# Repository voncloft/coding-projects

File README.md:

# Coding projects

A single-repository backup of the projects in this directory. Each project is stored here as ordinary files, so a clone or GitHub source download includes the project contents without submodules.

This repository starts with one snapshot of the current files. Earlier individual-project Git histories are not imported.

## Restore

```sh
git clone git@github.com:voncloft/coding-projects.git
cd coding-projects
```

Each project has its own build instructions and dependencies. Source code, required assets, CAD designs, firmware sources, and documentation are included. Build directories, compiled programs and libraries, firmware images, packaged browser extensions, runtime logs, local credentials, and development caches are excluded. Reinstall dependencies, rebuild the projects, and restore any credentials separately after reinstalling the OS.

## Update the backup

Run these commands from the top-level `coding-projects` directory:

```sh
git add -A
git commit -m "Update project backup"
git push
```

The projects retain their individual licenses and third-party notices. The keyboard project's existing engineering-audit and manufacturing-hold status is unchanged.

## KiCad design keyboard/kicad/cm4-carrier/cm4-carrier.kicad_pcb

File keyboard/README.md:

# Keyboard Revision H engineering audit

**Manufacturing HOLD. No approved replacement supplier ZIP.**

Start with [START-HERE.md](START-HERE.md), [current checks](CHECK-RESULTS.md) and [open items](OPEN-ITEMS.md). This folder holds the current KiCad, enclosure, parts, firmware and software work. Revision G must not be built.

Passing rule checks and software fixtures do not establish hardware qualification. Outstanding electrical review items and all physical acceptance measurements remain open. The owner’s live system has not been installed to, flashed or reconfigured.

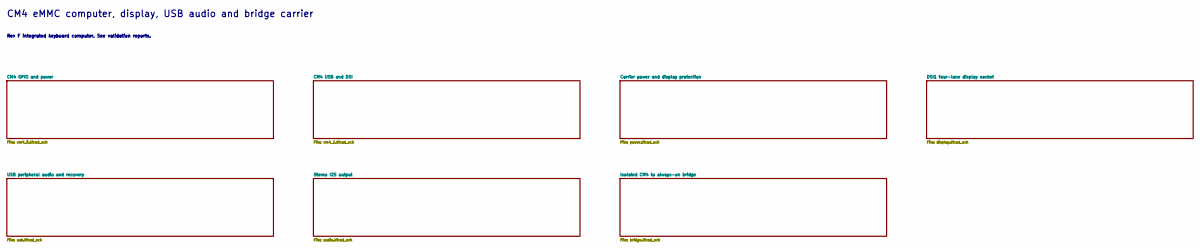
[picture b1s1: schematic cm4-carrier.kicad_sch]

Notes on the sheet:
CM4 eMMC computer, display, USB audio and bridge carrier
Rev F integrated keyboard computer. See validation reports.

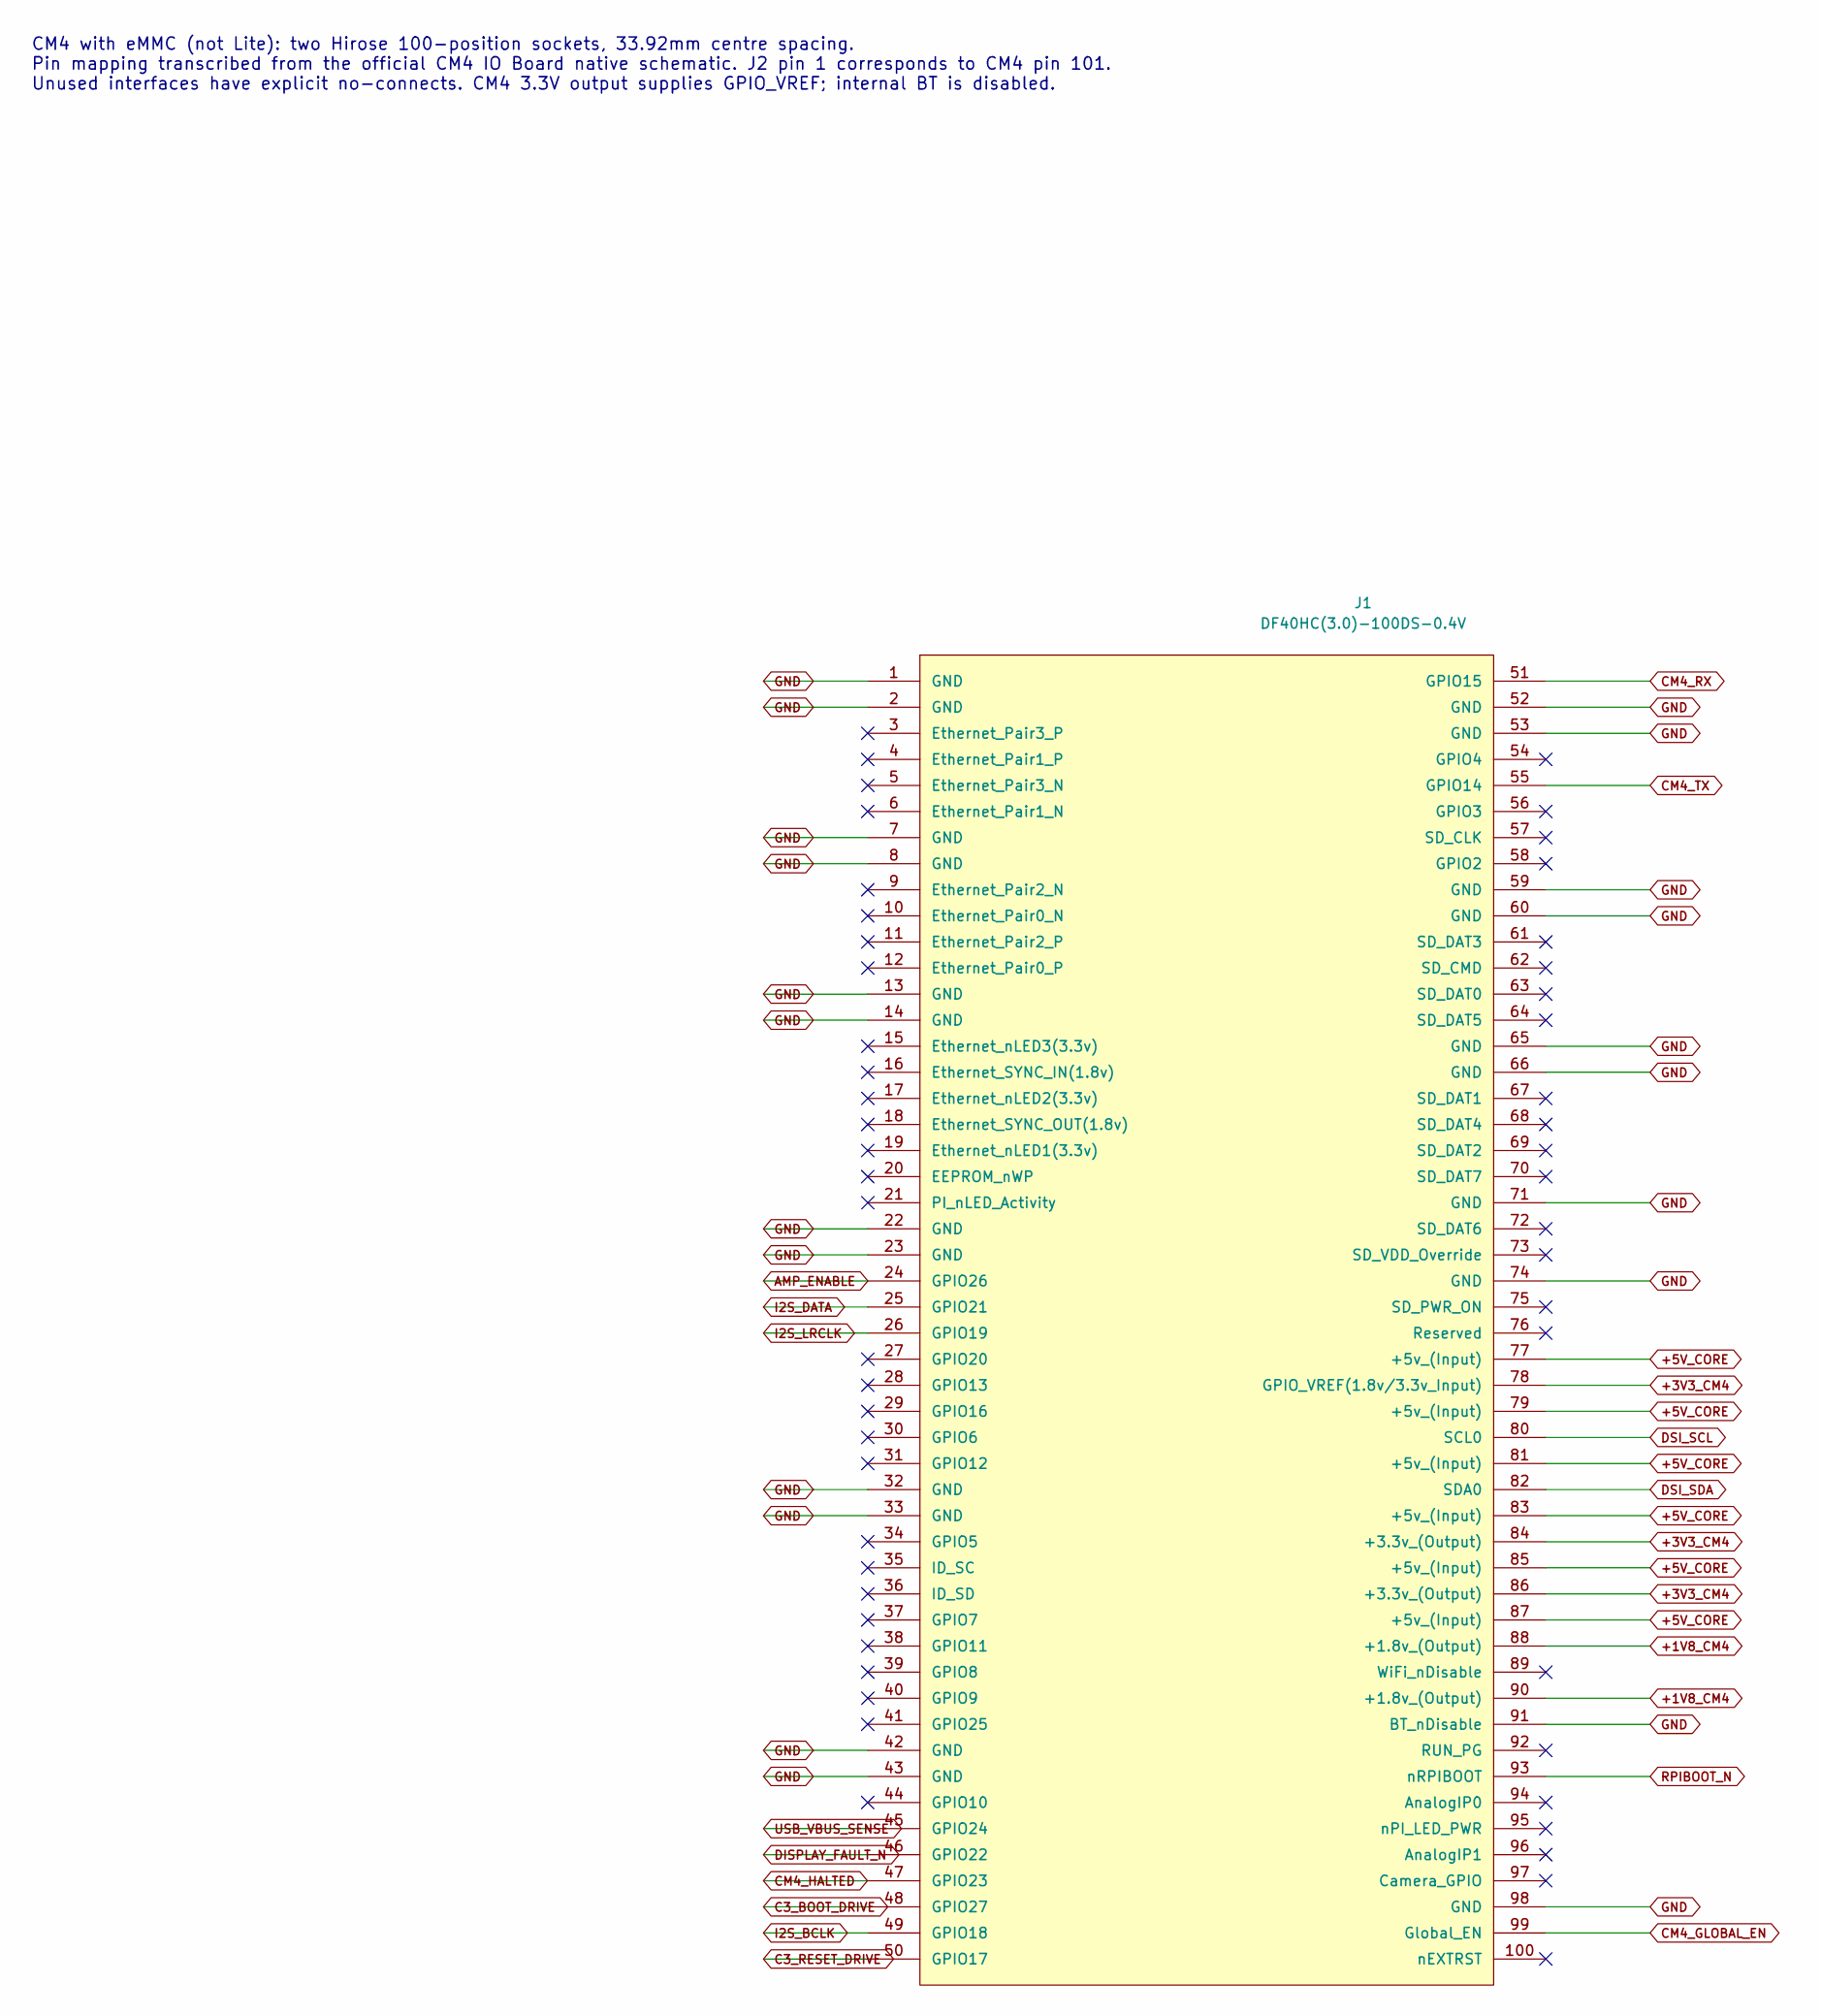
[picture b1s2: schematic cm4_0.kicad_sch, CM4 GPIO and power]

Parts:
J1: DF40HC(3.0)-100DS-0.4V; Hirose_DF40HC(3.0)-100DS-0.4V_2x50_P0.4mm; MPN DF40HC(3.0)-100DS-0.4V(51)

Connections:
+1V8_CM4: J1.88 (+1.8v_(Output)), J1.90 (+1.8v_(Output)); also elsewhere on the board
+3V3_CM4: J1.78 (GPIO_VREF(1.8v/3.3v_Input)), J1.84 (+3.3v_(Output)), J1.86 (+3.3v_(Output)); also elsewhere on the board
+5V_CORE: J1.77 (+5v_(Input)), J1.79 (+5v_(Input)), J1.81 (+5v_(Input)), J1.83 (+5v_(Input)), J1.85 (+5v_(Input)), J1.87 (+5v_(Input)); also elsewhere on the board
AMP_ENABLE: J1.24 (GPIO26); also elsewhere on the board
C3_BOOT_DRIVE: J1.48 (GPIO27); also elsewhere on the board
C3_RESET_DRIVE: J1.50 (GPIO17); also elsewhere on the board
CM4_GLOBAL_EN: J1.99 (Global_EN); also elsewhere on the board
CM4_HALTED: J1.47 (GPIO23); also elsewhere on the board
CM4_RX: J1.51 (GPIO15); also elsewhere on the board
CM4_TX: J1.55 (GPIO14); also elsewhere on the board
DISPLAY_FAULT_N: J1.46 (GPIO22); also elsewhere on the board
DSI_SCL: J1.80 (SCL0); also elsewhere on the board
DSI_SDA: J1.82 (SDA0); also elsewhere on the board
GND: J1.1 (GND), J1.2 (GND), J1.7 (GND), J1.8 (GND), J1.13 (GND), J1.14 (GND), J1.22 (GND), J1.23 (GND), J1.32 (GND), J1.33 (GND), J1.42 (GND), J1.43 (GND), J1.52 (GND), J1.53 (GND), J1.59 (GND), J1.60 (GND), J1.65 (GND), J1.66 (GND), J1.71 (GND), J1.74 (GND), J1.91 (BT_nDisable), J1.98 (GND); also elsewhere on the board
I2S_BCLK: J1.49 (GPIO18); also elsewhere on the board
I2S_DATA: J1.25 (GPIO21); also elsewhere on the board
I2S_LRCLK: J1.26 (GPIO19); also elsewhere on the board
RPIBOOT_N: J1.93 (nRPIBOOT); also elsewhere on the board
USB_VBUS_SENSE: J1.45 (GPIO24); also elsewhere on the board

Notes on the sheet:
CM4 with eMMC (not Lite): two Hirose 100-position sockets, 33.92mm centre spacing. Pin mapping transcribed from the official CM4 IO Board native schematic. J2 pin 1 corresponds to CM4 pin 101. Unused interfaces have explicit no-connects. CM4 3.3V output supplies GPIO_VREF; internal BT is disabled.

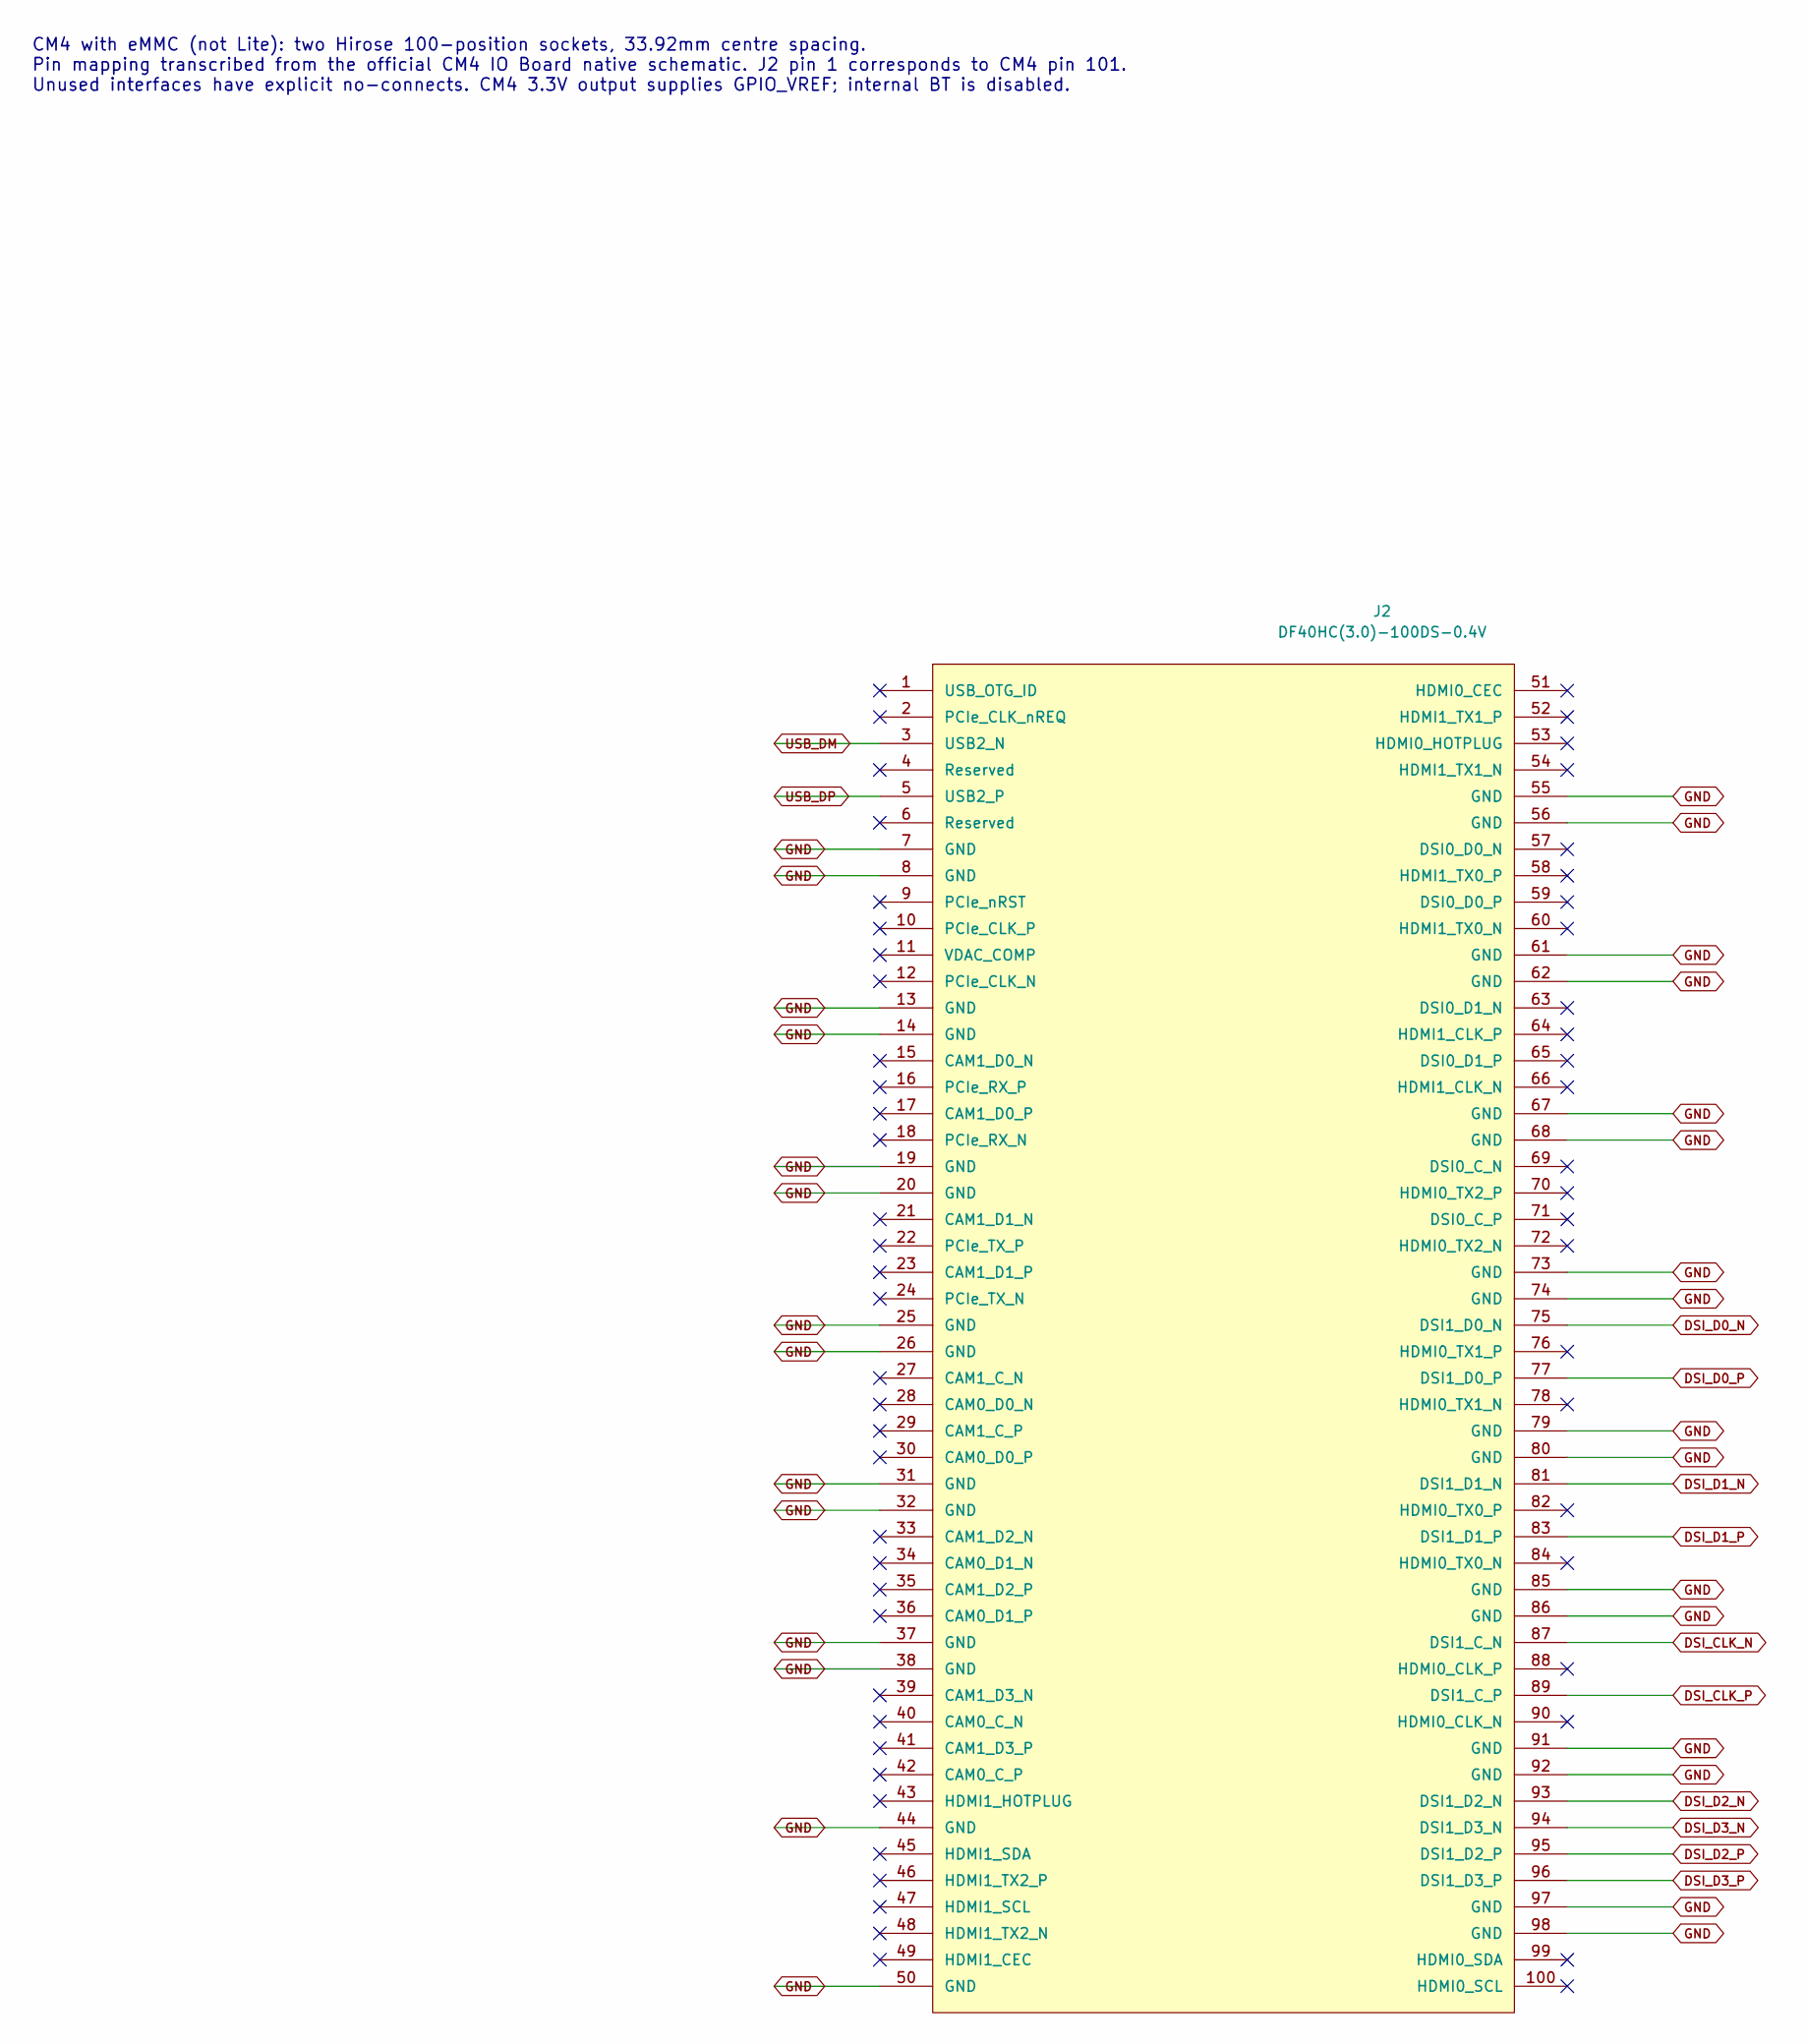
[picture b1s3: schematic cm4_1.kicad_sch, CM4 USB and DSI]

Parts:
J2: DF40HC(3.0)-100DS-0.4V; Hirose_DF40HC(3.0)-100DS-0.4V_2x50_P0.4mm; MPN DF40HC(3.0)-100DS-0.4V(51)

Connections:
DSI_CLK_N: J2.87 (DSI1_C_N); also elsewhere on the board
DSI_CLK_P: J2.89 (DSI1_C_P); also elsewhere on the board
DSI_D0_N: J2.75 (DSI1_D0_N); also elsewhere on the board
DSI_D0_P: J2.77 (DSI1_D0_P); also elsewhere on the board
DSI_D1_N: J2.81 (DSI1_D1_N); also elsewhere on the board
DSI_D1_P: J2.83 (DSI1_D1_P); also elsewhere on the board
DSI_D2_N: J2.93 (DSI1_D2_N); also elsewhere on the board
DSI_D2_P: J2.95 (DSI1_D2_P); also elsewhere on the board
DSI_D3_N: J2.94 (DSI1_D3_N); also elsewhere on the board
DSI_D3_P: J2.96 (DSI1_D3_P); also elsewhere on the board
GND: J2.7 (GND), J2.8 (GND), J2.13 (GND), J2.14 (GND), J2.19 (GND), J2.20 (GND), J2.25 (GND), J2.26 (GND), J2.31 (GND), J2.32 (GND), J2.37 (GND), J2.38 (GND), J2.44 (GND), J2.50 (GND), J2.55 (GND), J2.56 (GND), J2.61 (GND), J2.62 (GND), J2.67 (GND), J2.68 (GND), J2.73 (GND), J2.74 (GND), J2.79 (GND), J2.80 (GND), J2.85 (GND), J2.86 (GND), J2.91 (GND), J2.92 (GND), J2.97 (GND), J2.98 (GND); also elsewhere on the board
USB_DM: J2.3 (USB2_N); also elsewhere on the board
USB_DP: J2.5 (USB2_P); also elsewhere on the board

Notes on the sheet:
CM4 with eMMC (not Lite): two Hirose 100-position sockets, 33.92mm centre spacing. Pin mapping transcribed from the official CM4 IO Board native schematic. J2 pin 1 corresponds to CM4 pin 101. Unused interfaces have explicit no-connects. CM4 3.3V output supplies GPIO_VREF; internal BT is disabled.

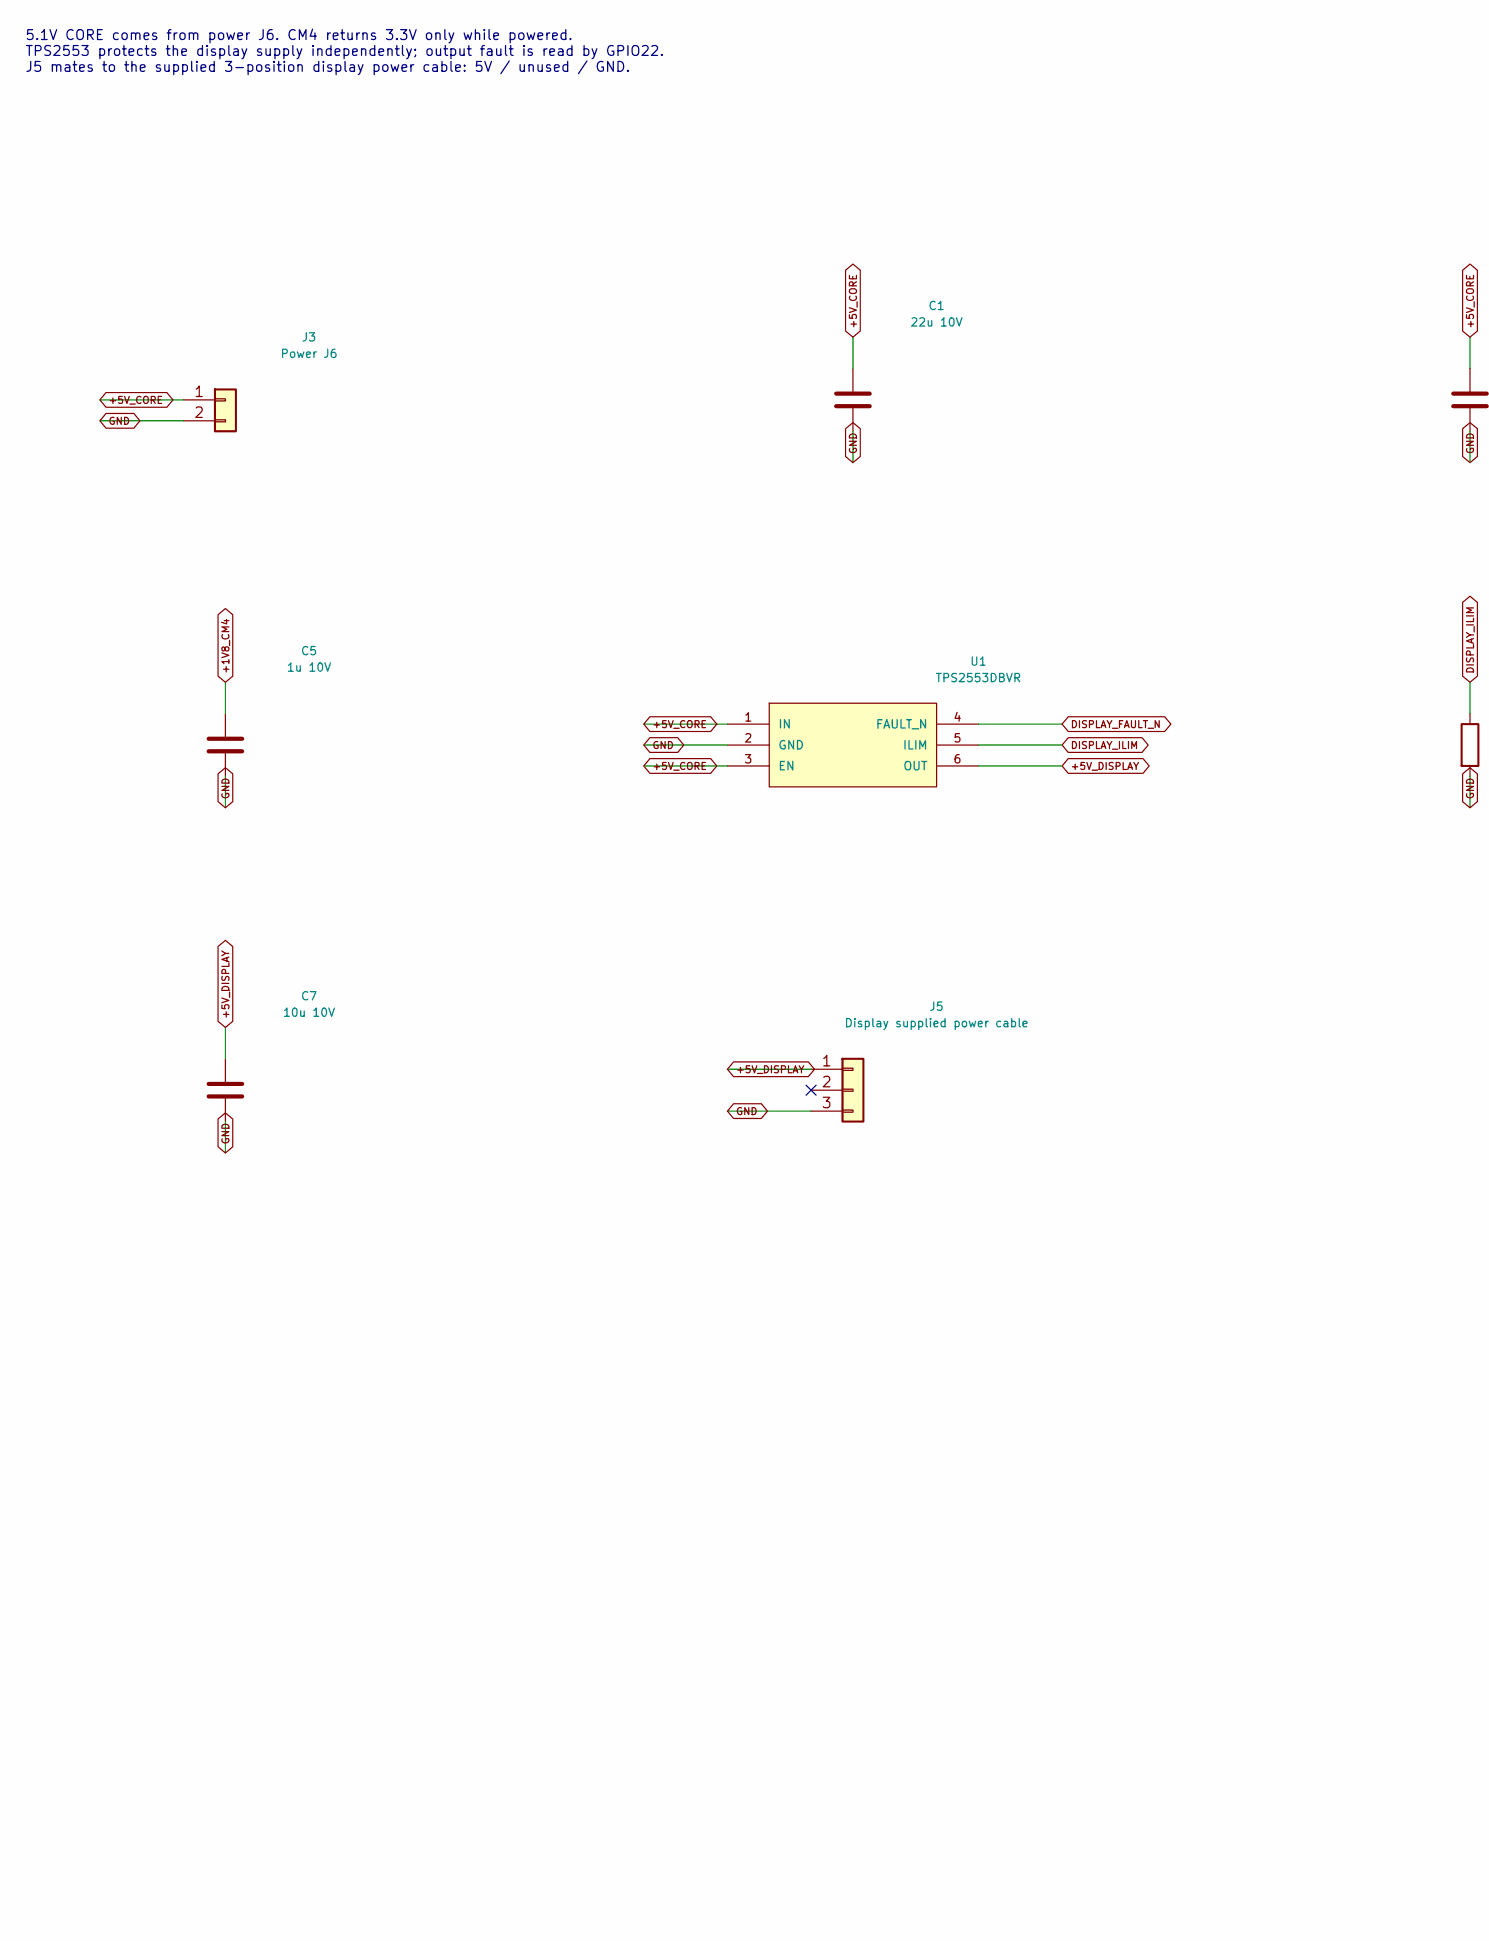
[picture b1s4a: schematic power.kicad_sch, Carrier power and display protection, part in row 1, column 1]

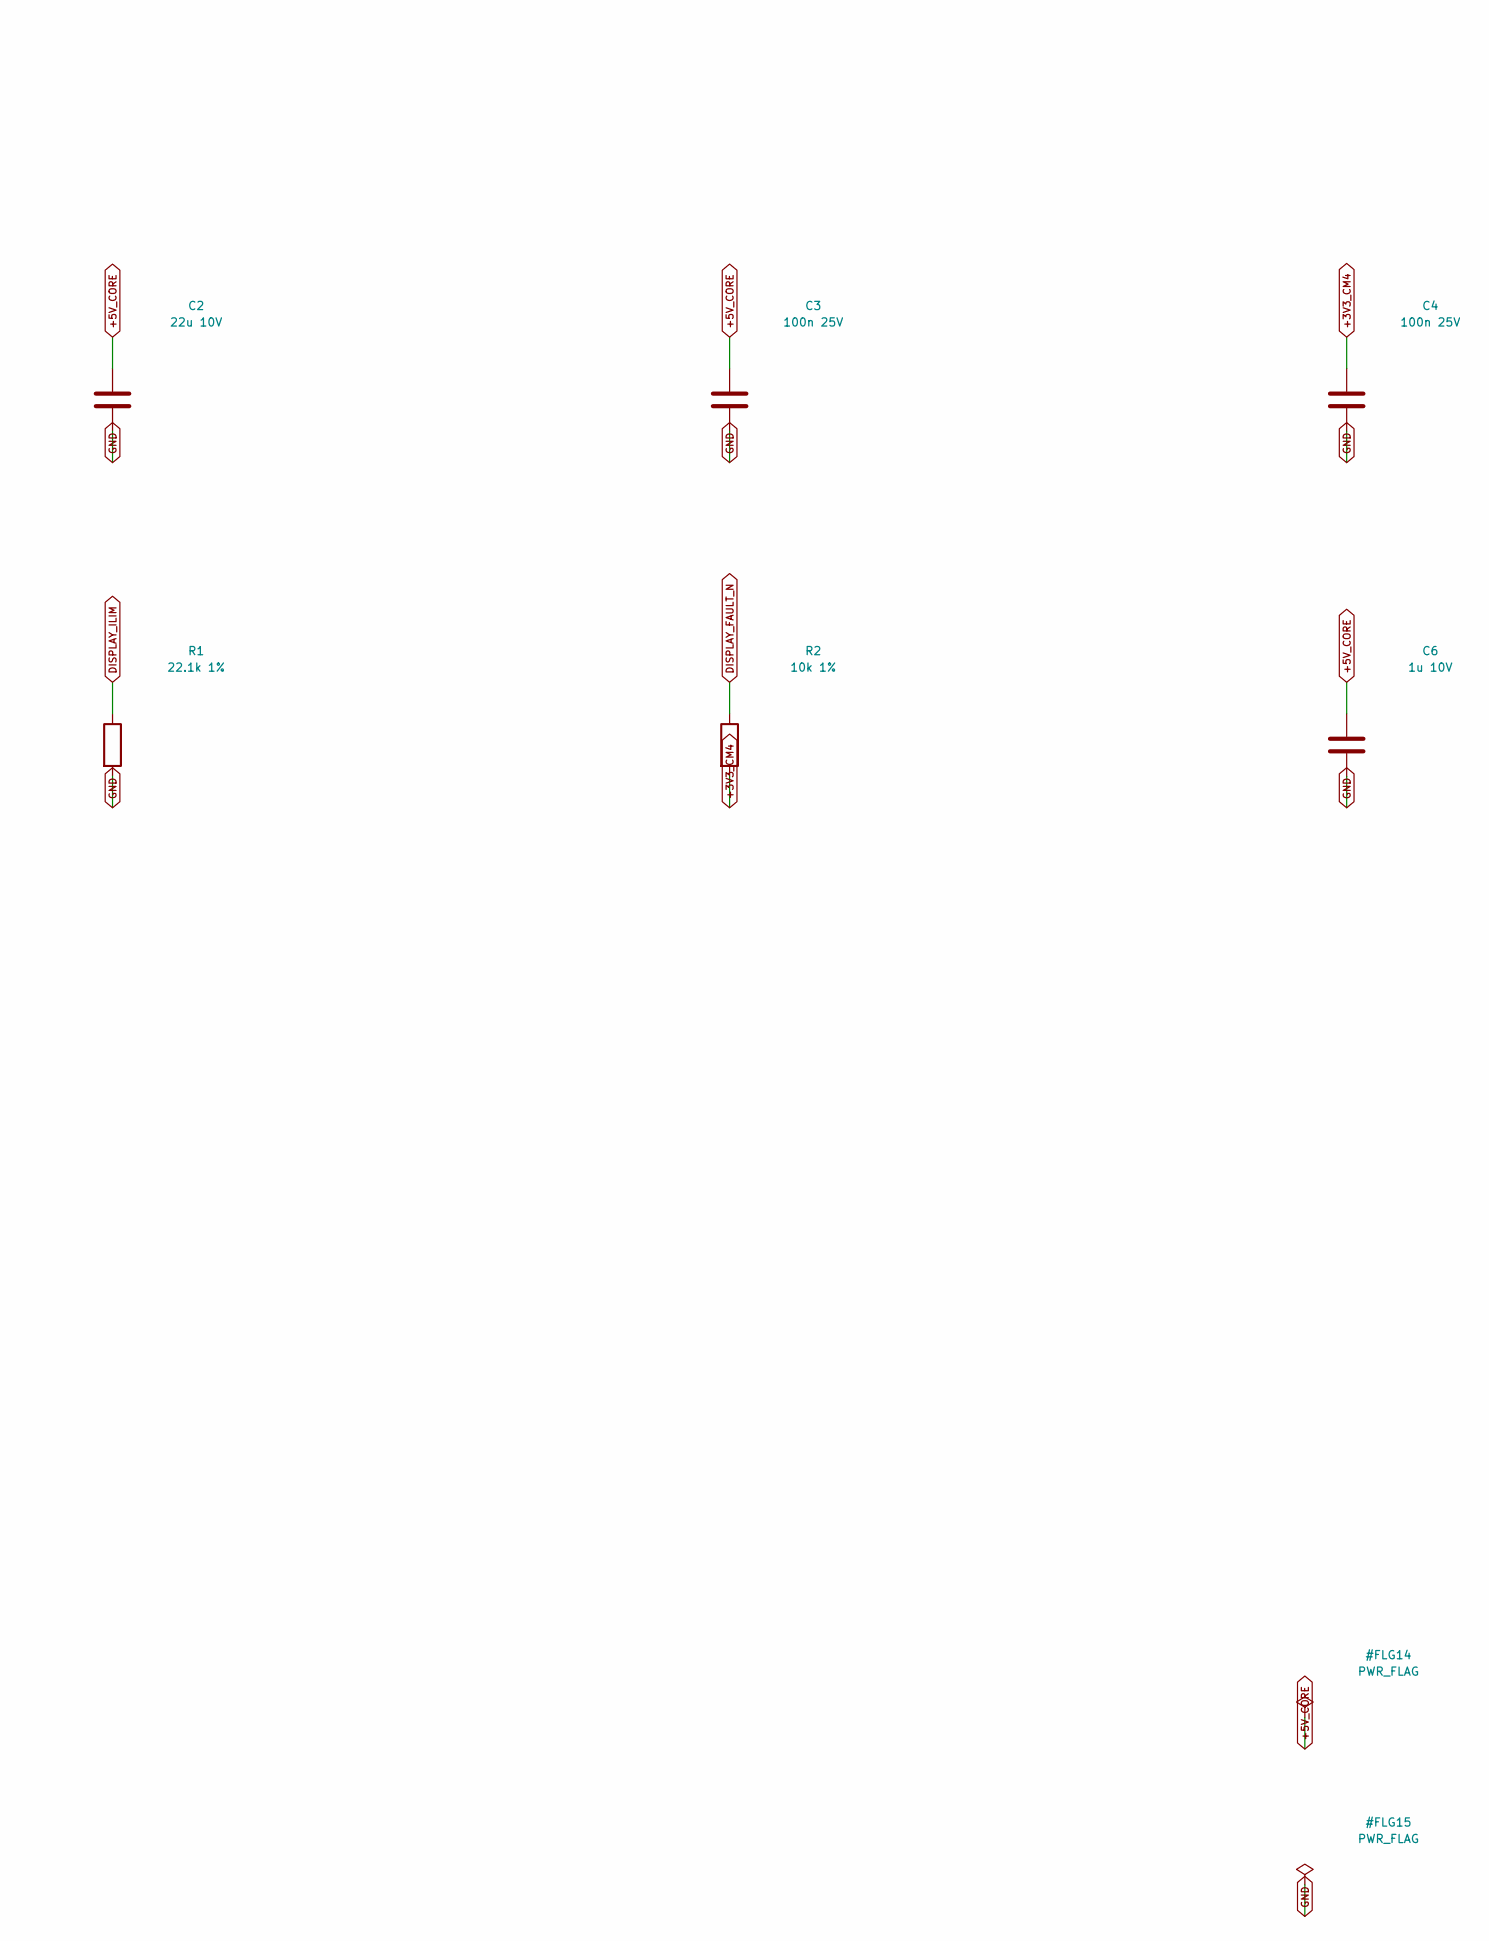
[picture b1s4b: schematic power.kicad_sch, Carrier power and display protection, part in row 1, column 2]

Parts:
C1, C2: 22u 10V; C_0805_2012Metric
C3, C4: 100n 25V; C_0603_1608Metric
C5, C6: 1u 10V; C_0603_1608Metric
C7: 10u 10V; C_0805_2012Metric
J3: Power J6; JST_VH_B2P-VH_1x02_P3.96mm_Vertical
J5: Display supplied power cable; PinHeader_1x03_P2.54mm_Vertical; MPN M20-9990345
R1: 22.1k 1%; R_0603_1608Metric
R2: 10k 1%; R_0603_1608Metric
U1: TPS2553DBVR; SOT-23-6; MPN TPS2553DBVR; JLCPCB C55266

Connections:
+1V8_CM4: C5.1; also elsewhere on the board
+3V3_CM4: C4.1, R2.2; also elsewhere on the board
+5V_CORE: C1.1, C2.1, C3.1, C6.1, J3.1, U1.1 (IN), U1.3 (EN); also elsewhere on the board
+5V_DISPLAY: C7.1, J5.1, U1.6 (OUT)
DISPLAY_FAULT_N: R2.1, U1.4 (FAULT_N); also elsewhere on the board
DISPLAY_ILIM: R1.1, U1.5 (ILIM)
GND: C1.2, C2.2, C3.2, C4.2, C5.2, C6.2, C7.2, J3.2, J5.3, R1.2, U1.2 (GND); also elsewhere on the board

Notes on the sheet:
5.1V CORE comes from power J6. CM4 returns 3.3V only while powered. TPS2553 protects the display supply independently; output fault is read by GPIO22. J5 mates to the supplied 3-position display power cable: 5V / unused / GND.

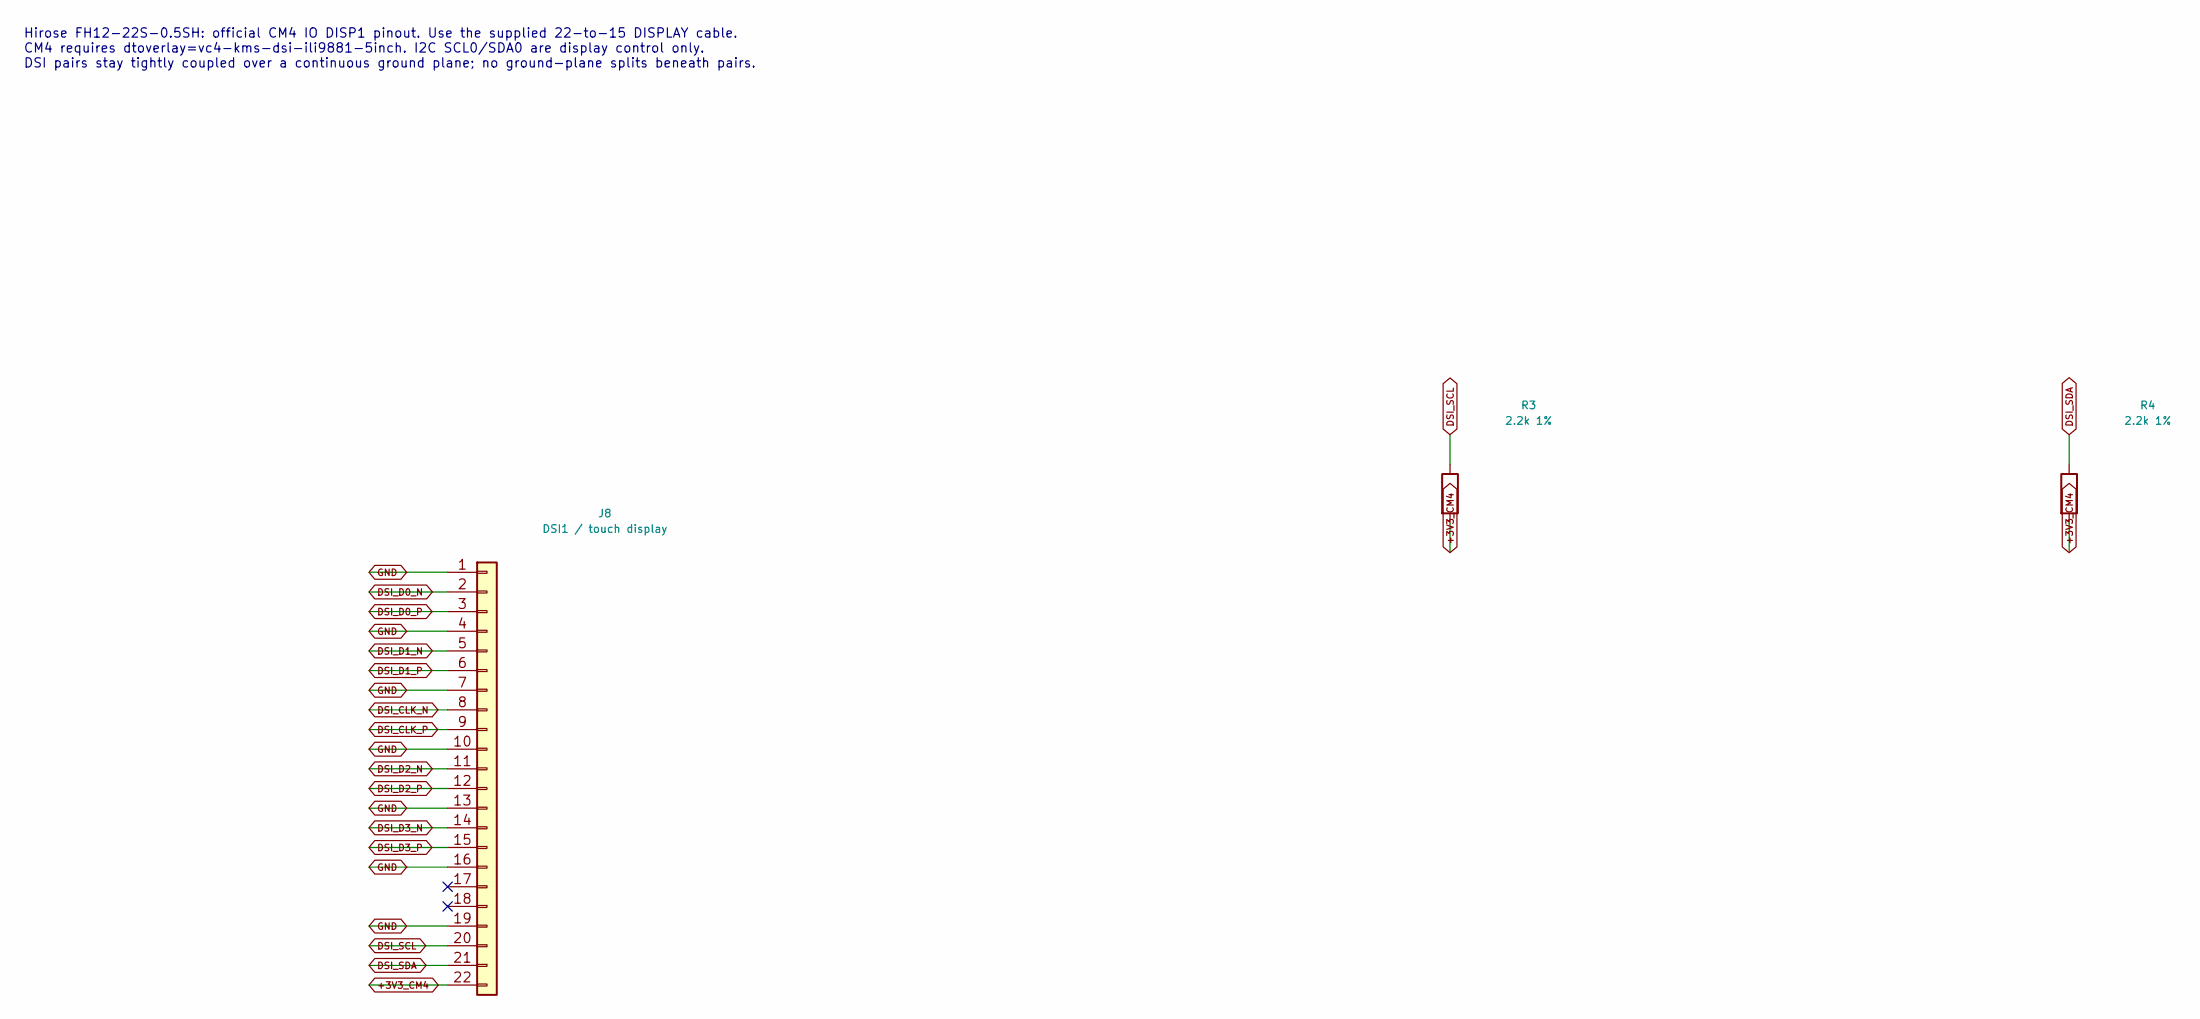
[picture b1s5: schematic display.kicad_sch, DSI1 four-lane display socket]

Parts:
J8: DSI1 / touch display; Hirose_FH12-22S-0.5SH_1x22-1MP_P0.50mm_Horizontal; MPN FH12-22S-0.5SH(55)
R3, R4: 2.2k 1%; R_0603_1608Metric

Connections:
+3V3_CM4: J8.22, R3.2, R4.2; also elsewhere on the board
DSI_CLK_N: J8.8; also elsewhere on the board
DSI_CLK_P: J8.9; also elsewhere on the board
DSI_D0_N: J8.2; also elsewhere on the board
DSI_D0_P: J8.3; also elsewhere on the board
DSI_D1_N: J8.5; also elsewhere on the board
DSI_D1_P: J8.6; also elsewhere on the board
DSI_D2_N: J8.11; also elsewhere on the board
DSI_D2_P: J8.12; also elsewhere on the board
DSI_D3_N: J8.14; also elsewhere on the board
DSI_D3_P: J8.15; also elsewhere on the board
DSI_SCL: J8.20, R3.1; also elsewhere on the board
DSI_SDA: J8.21, R4.1; also elsewhere on the board
GND: J8.1, J8.4, J8.7, J8.10, J8.13, J8.16, J8.19; also elsewhere on the board

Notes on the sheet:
Hirose FH12-22S-0.5SH: official CM4 IO DISP1 pinout. Use the supplied 22-to-15 DISPLAY cable. CM4 requires dtoverlay=vc4-kms-dsi-ili9881-5inch. I2C SCL0/SDA0 are display control only. DSI pairs stay tightly coupled over a continuous ground plane; no ground-plane splits beneath pairs.

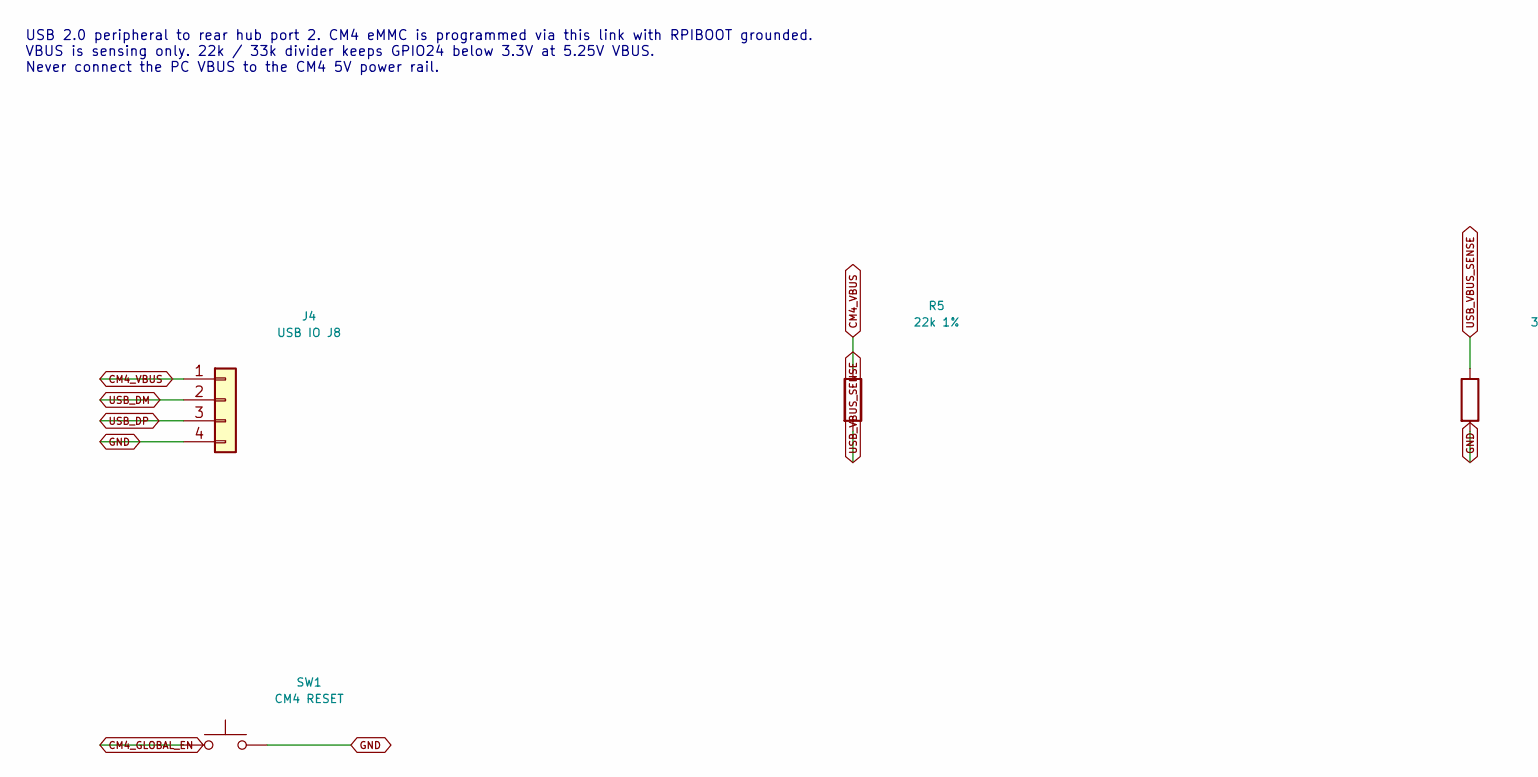
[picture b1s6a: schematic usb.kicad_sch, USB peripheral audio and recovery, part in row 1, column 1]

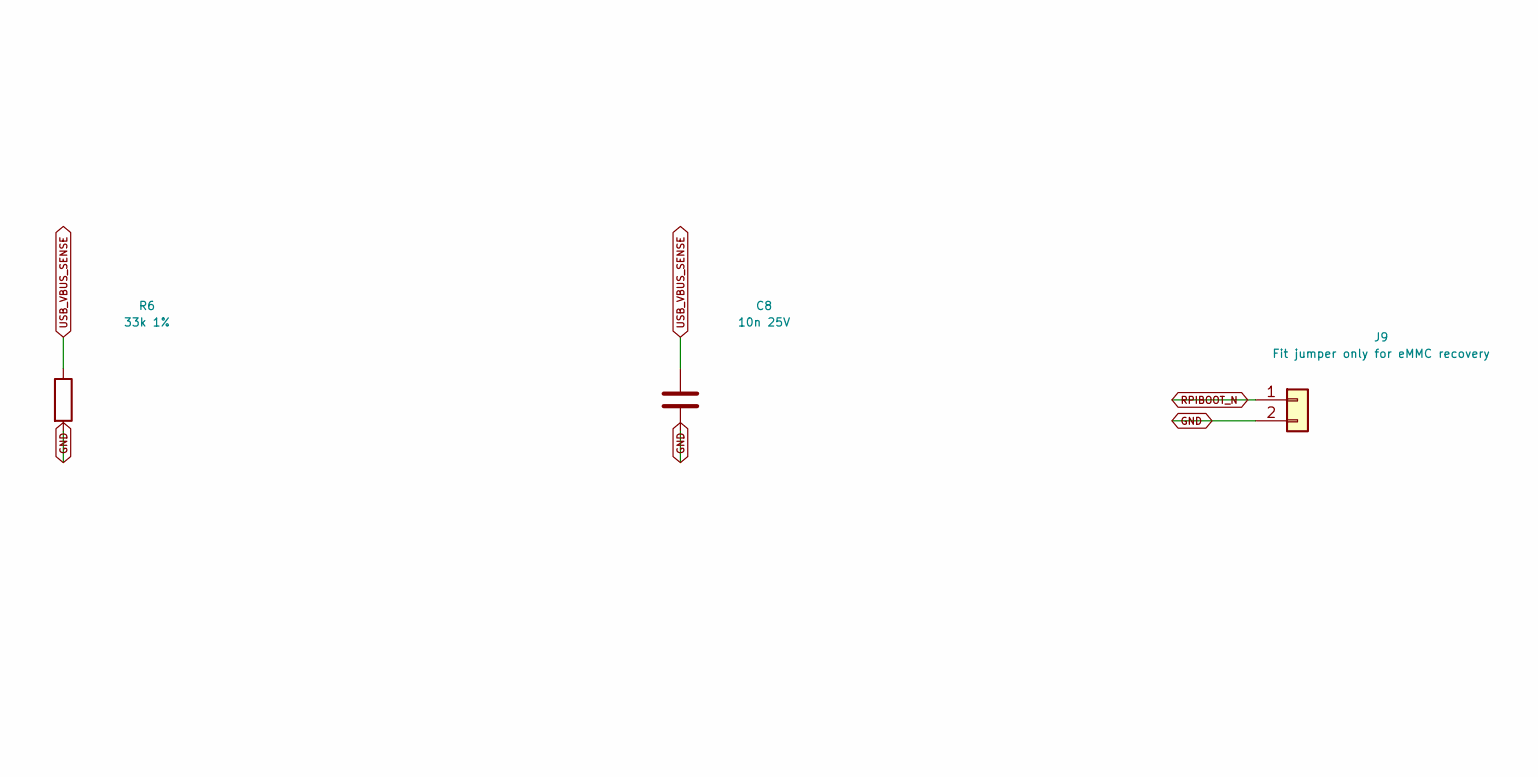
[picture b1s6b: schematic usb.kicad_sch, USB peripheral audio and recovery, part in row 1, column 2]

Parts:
C8: 10n 25V; C_0603_1608Metric
J4: USB IO J8; JST_GH_BM04B-GHS-TBT_1x04-1MP_P1.25mm_Vertical
J9: Fit jumper only for eMMC recovery; PinHeader_1x02_P2.54mm_Vertical; MPN M20-9990245
R5: 22k 1%; R_0603_1608Metric
R6: 33k 1%; R_0603_1608Metric
SW1: CM4 RESET; SW_SPST_TL3342; MPN TL3342F160QG

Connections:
CM4_GLOBAL_EN: SW1.1; also elsewhere on the board
CM4_VBUS: J4.1, R5.1
GND: C8.2, J4.4, J9.2, R6.2, SW1.2; also elsewhere on the board
RPIBOOT_N: J9.1; also elsewhere on the board
USB_DM: J4.2; also elsewhere on the board
USB_DP: J4.3; also elsewhere on the board
USB_VBUS_SENSE: C8.1, R5.2, R6.1; also elsewhere on the board

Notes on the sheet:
USB 2.0 peripheral to rear hub port 2. CM4 eMMC is programmed via this link with RPIBOOT grounded. VBUS is sensing only. 22k / 33k divider keeps GPIO24 below 3.3V at 5.25V VBUS. Never connect the PC VBUS to the CM4 5V power rail.
